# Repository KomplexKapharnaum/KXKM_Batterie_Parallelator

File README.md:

<h1 align="center">KXKM Batterie Parallelator</h1>

<p align="center">
  <strong>Battery Management Unit for parallel 24-30V packs</strong><br>
  Up to 32 batteries &middot; ESP32-S3 &middot; BLE + MQTT + InfluxDB &middot; iOS companion app
</p>

<p align="center">

</p>

---

## Overview

The **KXKM Batterie Parallelator** is an embedded Battery Management Unit (BMU) that safely parallels multiple battery packs (24-30V) for off-grid stage installations. Each battery is individually monitored (voltage, current, temperature) and can be disconnected in microseconds via MOSFET switches.

Built by [L'Electron Rare](https://lelectronrare.fr) for [KompleX KapharnaüM](https://komplex-kapharnaum.net) (Villeurbanne, France) — a live arts company deploying digital scenography in public spaces without grid power.

### Key Features

| Feature | Description |
|---------|-------------|
| Per-battery protection | Under/over-voltage, over-current, imbalance detection |
| Auto-reconnection | Exponential backoff with permanent lock after 5 faults |
| Soft-balancing | Duty-cycling with opportunistic R_int measurement |
| Victron integration | BLE Instant Readout + GATT SmartShunt emulation + device scanner |
| Touchscreen UI | 320x240 LVGL display with battery grid, SOH, charts |
| iOS companion app | BLE real-time monitoring, offline cache, role-based access |
| Cloud telemetry | MQTT + InfluxDB + Grafana with offline persistence |
| OTA updates | Dual-partition with automatic rollback |

---

## Quick Start

```bash
# ESP-IDF firmware (production)
cd firmware-idf
source ~/esp/esp-idf/export.sh
idf.py build
idf.py -p /dev/cu.usbmodem* flash monitor

# PlatformIO (legacy Arduino)
pio run -e kxkm-s3-16MB --target upload

# Run all tests (no hardware needed)
pio test -e sim-host          # 13 PlatformIO tests
cd firmware-idf && idf.py build  # 13 ESP-IDF host tests

# Cloud stack (kxkm-ai server)
cd kxkm-api && cp .env.example .env && docker compose up -d
```

---

## Architecture

```
                          ┌──────────────────────────┐
                          │    ESP32-S3-BOX-3         │
                          │    320x240 LVGL display   │
                          │    NimBLE + WiFi          │
                          └─────────┬────────────────┘
                                    │ I2C 50kHz
                    ┌───────────────┼───────────────┐
                    │               │               │
              ┌─────▼─────┐  ┌─────▼─────┐  ┌─────▼─────┐
              │ TCA9535    │  │ TCA9535   │  │  ...×8    │
              │ 4× MOSFET  │  │ 4× LED   │  │           │
              └─────┬─────┘  └───────────┘  └───────────┘
                    │
              ┌─────▼─────┐
              │ INA237 ×4  │  ← per TCA (voltage + current)
              └───────────┘

    ┌──────────────────────────────────────────────────────┐
    │                    Cloud Stack                        │
    │  BMU ──MQTT──► Mosquitto ──► Telegraf ──► InfluxDB   │
    │                                              │       │
    │  iPhone ◄──BLE──► BMU    Grafana ◄───────────┘       │
    │  iPhone ◄──REST──► FastAPI ◄─────────────────┘       │
    └──────────────────────────────────────────────────────┘
```

### Firmware Components (ESP-IDF, 25 modules)

| Component | Role |
|-----------|------|
| `bmu_protection` | State machine: 5 states, 5 criteria, permanent lock |
| `bmu_balancer` | Soft-balancing duty-cycling + R_int measurement |
| `bmu_ina237` | 16× INA237 power monitors (2mΩ shunt) |
| `bmu_tca9535` | 8× GPIO expanders (switches + LEDs) |
| `bmu_ble` | NimBLE 4 GATT services + Victron SmartShunt |
| `bmu_ble_victron` | Victron Instant Readout (AES-CTR encrypted ads) |
| `bmu_ble_victron_scan` | BLE central scanner for Victron devices |
| `bmu_display` | LVGL: battery grid, pack info, SOH, charts, swipe |
| `bmu_influx` + `_store` | InfluxDB client + offline FAT/SD persistence |
| `bmu_mqtt` | ESP-MQTT with auth credentials |
| `bmu_vedirect` | Victron VE.Direct UART parser (solar charger) |
| `bmu_rint` | Internal resistance pulse measurement |
| `bmu_web` | HTTP + WebSocket with token auth + rate limiting |
| `bmu_config` | NVS runtime config + Victron device keys |
| `bmu_storage` | NVS, FAT, SPIFFS, SD card, USB MSC |
| `bmu_ota` | OTA firmware update with rollback |

### Protection Logic

```
Nb_switch < 5   →  Reconnect immediately when condition clears
Nb_switch == 5  →  10-second delay before reconnection
Nb_switch > 5   →  Permanent lock (blinking red LED) until reboot
```

| Threshold | Default | Configurable |
|-----------|---------|:------------:|
| Min voltage | 24,000 mV | via Kconfig + NVS |
| Max voltage | 30,000 mV | via Kconfig + NVS |
| Max current | 10,000 mA | via Kconfig + NVS |
| Imbalance | 1,000 mV | via Kconfig + NVS |
| Reconnect delay | 10,000 ms | via Kconfig |
| Switch limit | 5 | via Kconfig |

### LED Behavior

| State | LED |
|-------|-----|
| Connected | Solid green |
| Disconnected | Solid red |
| Error | **Blinking red** (~1 Hz) |
| Locked | Solid red |

---

## iOS Companion App

<p align="center">
  <strong>KXKM BMU</strong> &mdash; SwiftUI + CoreBluetooth
</p>

| Feature | Transport |
|---------|-----------|
| Real-time battery dashboard | BLE (2s poll) |
| Battery detail + voltage chart | BLE |
| Switch ON/OFF + reset | BLE (role-gated) |
| Protection config (0.025V/A step) | BLE |
| WiFi config for BMU | BLE |
| Audit trail + filtering | Local SQLDelight |
| Offline mode with cache indicator | Auto-fallback |
| SOH dashboard + R_int | BLE + REST |
| Victron device scanning | BLE passive |

**3 roles**: Admin (full), Technician (control), Viewer (read-only) — PIN + Face ID.

**Code**: `iosApp/` (Xcode, CoreBluetooth) + `kxkm-bmu-app/` (KMP Shared Kotlin)

---

## Victron BLE Integration

The BMU interacts with the Victron ecosystem via three mechanisms:

| Mechanism | Direction | Protocol |
|-----------|-----------|----------|
| Instant Readout | BMU → VictronConnect | AES-CTR encrypted advertising (PID 0xA389) |
| GATT SmartShunt | BMU → any BLE client | 9 read-only characteristics (V, I, SOC, Ah, TTG, T, alarm) |
| Device Scanner | Victron devices → BMU | Passive BLE scan, AES decrypt, 8 device cache |

Supported Victron record types: Solar (0x01), Battery (0x02), Inverter (0x03), DC-DC (0x04).

---

## Cloud Infrastructure

Docker stack on `kxkm-ai` server:

| Service | Port | Role |
|---------|------|------|
| Mosquitto | 1883, 9001 | MQTT broker (authenticated) |
| InfluxDB 2.7 | 8086 | Time-series storage (org=kxkm, bucket=bmu) |
| Telegraf | - | MQTT → InfluxDB bridge |
| FastAPI | 8400 | REST API (sync, history, audit) |
| Grafana 11 | 3001 | 3 dashboards (live, fleet, solar) |

**Setup**: `cp .env.example .env` — fill all secrets (API key, InfluxDB token, MQTT credentials, Grafana password, CORS origins). All secrets via `${...}` env vars, `chmod 600 .env`.

**Offline resilience**: when WiFi/InfluxDB is unreachable, telemetry is persisted to internal FAT flash (`/fatfs/influx/`) with 2-file rotation (512KB each). Automatic replay on reconnection.

---

## Testing

**26 tests total** — no hardware required.

### PlatformIO sim-host (13 tests)

```bash
pio test -e sim-host
```

| Suite | Tests | Covers |
|-------|:-----:|--------|
| `test_protection` | 10 | V/I/imbalance/lock state machine |
| `test_battery_route_validation` | - | Index bounds + state checks |
| `test_influx_buffer_codec` | - | InfluxDB line-protocol encoding |
| `test_web_mutation_rate_limit` | 3 | Sliding window + multi-IP |
| `test_web_route_security` | 9 | Constant-time token + Bearer |
| `test_ws_auth_flow` | 7 | Combined auth + rate limit |
| `test_mqtt_influx_codec` | 3 | JSON MQTT + topic parsing |
| `test_emulation_bench` | - | Emulation benchmark |

### ESP-IDF Host Tests (13 tests)

```bash
cd firmware-idf && idf.py build
```

| Suite | Tests | Covers |
|-------|:-----:|--------|
| `test_protection` | 13 | Full state machine (ESP-IDF) |
| `test_victron_gatt` | 8 | GATT encoding (V, SOC, alarm, TTG, T) |
| `test_victron_scan` | 5 | Payload parsing, expiry, MAC, CID |
| `test_ble_victron` | - | Battery/solar payload encoding |
| `test_vedirect_parser` | - | VE.Direct frame parsing |
| `test_rint` | - | R_int calculation |
| `test_config_labels` | - | Battery label management |
| `test_vrm_topics` | - | VRM topic generation |

### CI/CD Pipelines

| Pipeline | Trigger | Gate |
|----------|---------|------|
| `ci.yml` | push/PR | sim-host 13 tests pass |
| `sim-host-tests.yml` | push/PR | + S3 build + RAM ≤75% + Flash ≤85% |
| `esp-idf-ci.yml` | push/PR | + ESP-IDF host tests + flash ≤85% of 2MB OTA |

**Current flash usage**: 81% (1.69 MB / 2 MB OTA partition) — 19% headroom.

---

## Security Audit

**All findings resolved** as of 2026-04-07.

<details>
<summary><strong>Phase 1 — Migration (March 2026): 7/7 resolved</strong></summary>

| ID | Finding | Status |
|----|---------|--------|
| CRIT-001 | Obsolete function calls | ✅ |
| CRIT-002 | Unreliable global Nb_INA | ✅ |
| CRIT-003 | I2C access without mutex | ✅ |
| CRIT-004 | Missing mutex init | ✅ |
| HIGH-005 | WebSocket V/I race | ✅ |
| HIGH-006 | reconnect_time race | ✅ |
| HIGH-007 | Uninitialized globals | ✅ |

</details>

<details>
<summary><strong>Phase 2 — Deep audit (March-April 2026): 13/13 resolved</strong></summary>

| ID | Severity | Finding | Fix |
|----|----------|---------|-----|
| CRIT-A | Critical | mV/V unit mismatch | ESP-IDF: mV everywhere |
| CRIT-B | Critical | Imbalance vs config instead of fleet max | bmu_protection |
| CRIT-C | Critical | Deadlock in web switch | bmu_web |
| CRIT-D | Critical | Unauthenticated routes | bmu_web_security |
| HIGH-1 | High | Negative overcurrent ignored | Bidirectional factor |
| HIGH-2 | High | Unauthenticated WebSocket | Token on first frame |
| HIGH-3 | High | XSS in /log | cJSON null check |
| HIGH-4 | High | MQTT plaintext | Mosquitto auth + .env |
| HIGH-5 | High | I2C speed change unguarded | I2CLockGuard |
| HIGH-7 | High | Public battery_voltages[] | state_mutex |
| HIGH-8 | High | Influx task crash on SD fail | influx_store fallback |
| MED-1 | Medium | No permanent lock (F08) | BMU_STATE_LOCKED |
| MED-010 | Medium | mV/V harmonization | mV throughout |

</details>

<details>
<summary><strong>Infrastructure audit (April 2026): 5/5 resolved</strong></summary>

| Finding | Fix |
|---------|-----|
| Mosquitto anonymous access | Auth + password file |
| Hardcoded secrets in docker-compose | All via .env (chmod 600) |
| Default InfluxDB token | Rotated (44-char random) |
| CORS allow_origins=["*"] | Restricted via env var |
| Offline data loss | FAT/SD persistence + replay |

</details>

---

## Hardware

### PCB Revisions

| Version | Status | Files |
|---------|--------|-------|
| BMU v1 | Manufactured | `hardware/PCB/` |
| BMU v2 | Production-ready (ERC 0, BOM 107) | `hardware/pcb-bmu-v2/` |

### Key ICs

| IC | Package | Role | I2C Address |
|----|---------|------|-------------|
| INA237 | VSSOP-10 | Power monitor (V/I/P) | 0x40-0x4F (16 max) |
| TCA9535 | TSSOP-24 | GPIO expander (switches + LEDs) | 0x20-0x27 (8 max) |
| ISO1540 | SOIC-8 | Galvanic I2C isolator | - |
| IRF4905 | D2PAK | P-channel MOSFET (55V, 74A) | - |

### I2C Mapping

```
TCA_0 (0x20) → INA 0x40-0x43 → Batteries 1-4
TCA_1 (0x21) → INA 0x44-0x47 → Batteries 5-8
TCA_2 (0x22) → INA 0x48-0x4B → Batteries 9-12
TCA_3 (0x23) → INA 0x4C-0x4F → Batteries 13-16
```

Topology constraint: `Nb_TCA × 4 == Nb_INA` — mismatch triggers fail-safe (all OFF).

---

## Project Structure

```
KXKM_Batterie_Parallelator/
├── firmware-idf/          # ESP-IDF 5.4 firmware (25 components)
│   ├── components/        # Modular ESP-IDF components
│   ├── main/              # app_main entry point
│   └── test/              # Unity host tests (13 suites)
├── firmware/              # Legacy PlatformIO/Arduino firmware
│   ├── src/               # Source modules
│   ├── test/              # sim-host tests (8 suites, 13 tests)
│   └── lib/INA237/        # Local INA237 driver fork
├── iosApp/                # iOS SwiftUI app (CoreBluetooth)
├── kxkm-bmu-app/          # KMP shared Kotlin module
│   └── shared/            # Cross-platform domain logic
├── kxkm-api/              # Docker stack (Mosquitto, InfluxDB, FastAPI, Grafana)
├── hardware/              # KiCad schematics + Gerbers (v1 + v2)
├── specs/                 # Kill_LIFE gates (S0-S3)
├── docs/                  # Specs, plans, governance, research
├── grafana/dashboards/    # 3 Grafana dashboard JSONs
└── scripts/               # CI, QA, ML pipeline
```

---

## About KompleX KapharnaüM

[KompleX KapharnaüM](https://komplex-kapharnaum.net) is a live arts company based in Villeurbanne (Lyon, France), active for 20+ years in street arts, live performance, and digital creation. The company develops its own embedded hardware platform (K32, ESP32-based) and maintains open-source tools on [GitHub](https://github.com/KomplexKapharnaum).

---

## License

[GNU General Public License v3.0](LICENSE)

---

<p align="center">
  <sub>Built with ESP-IDF, LVGL, NimBLE, SwiftUI, FastAPI, InfluxDB, and Grafana.</sub><br>
  <sub>Developed by <a href="https://lelectronrare.fr">L'Electron Rare</a> for <a href="https://komplex-kapharnaum.net">KompleX KapharnaüM</a></sub>
</p>

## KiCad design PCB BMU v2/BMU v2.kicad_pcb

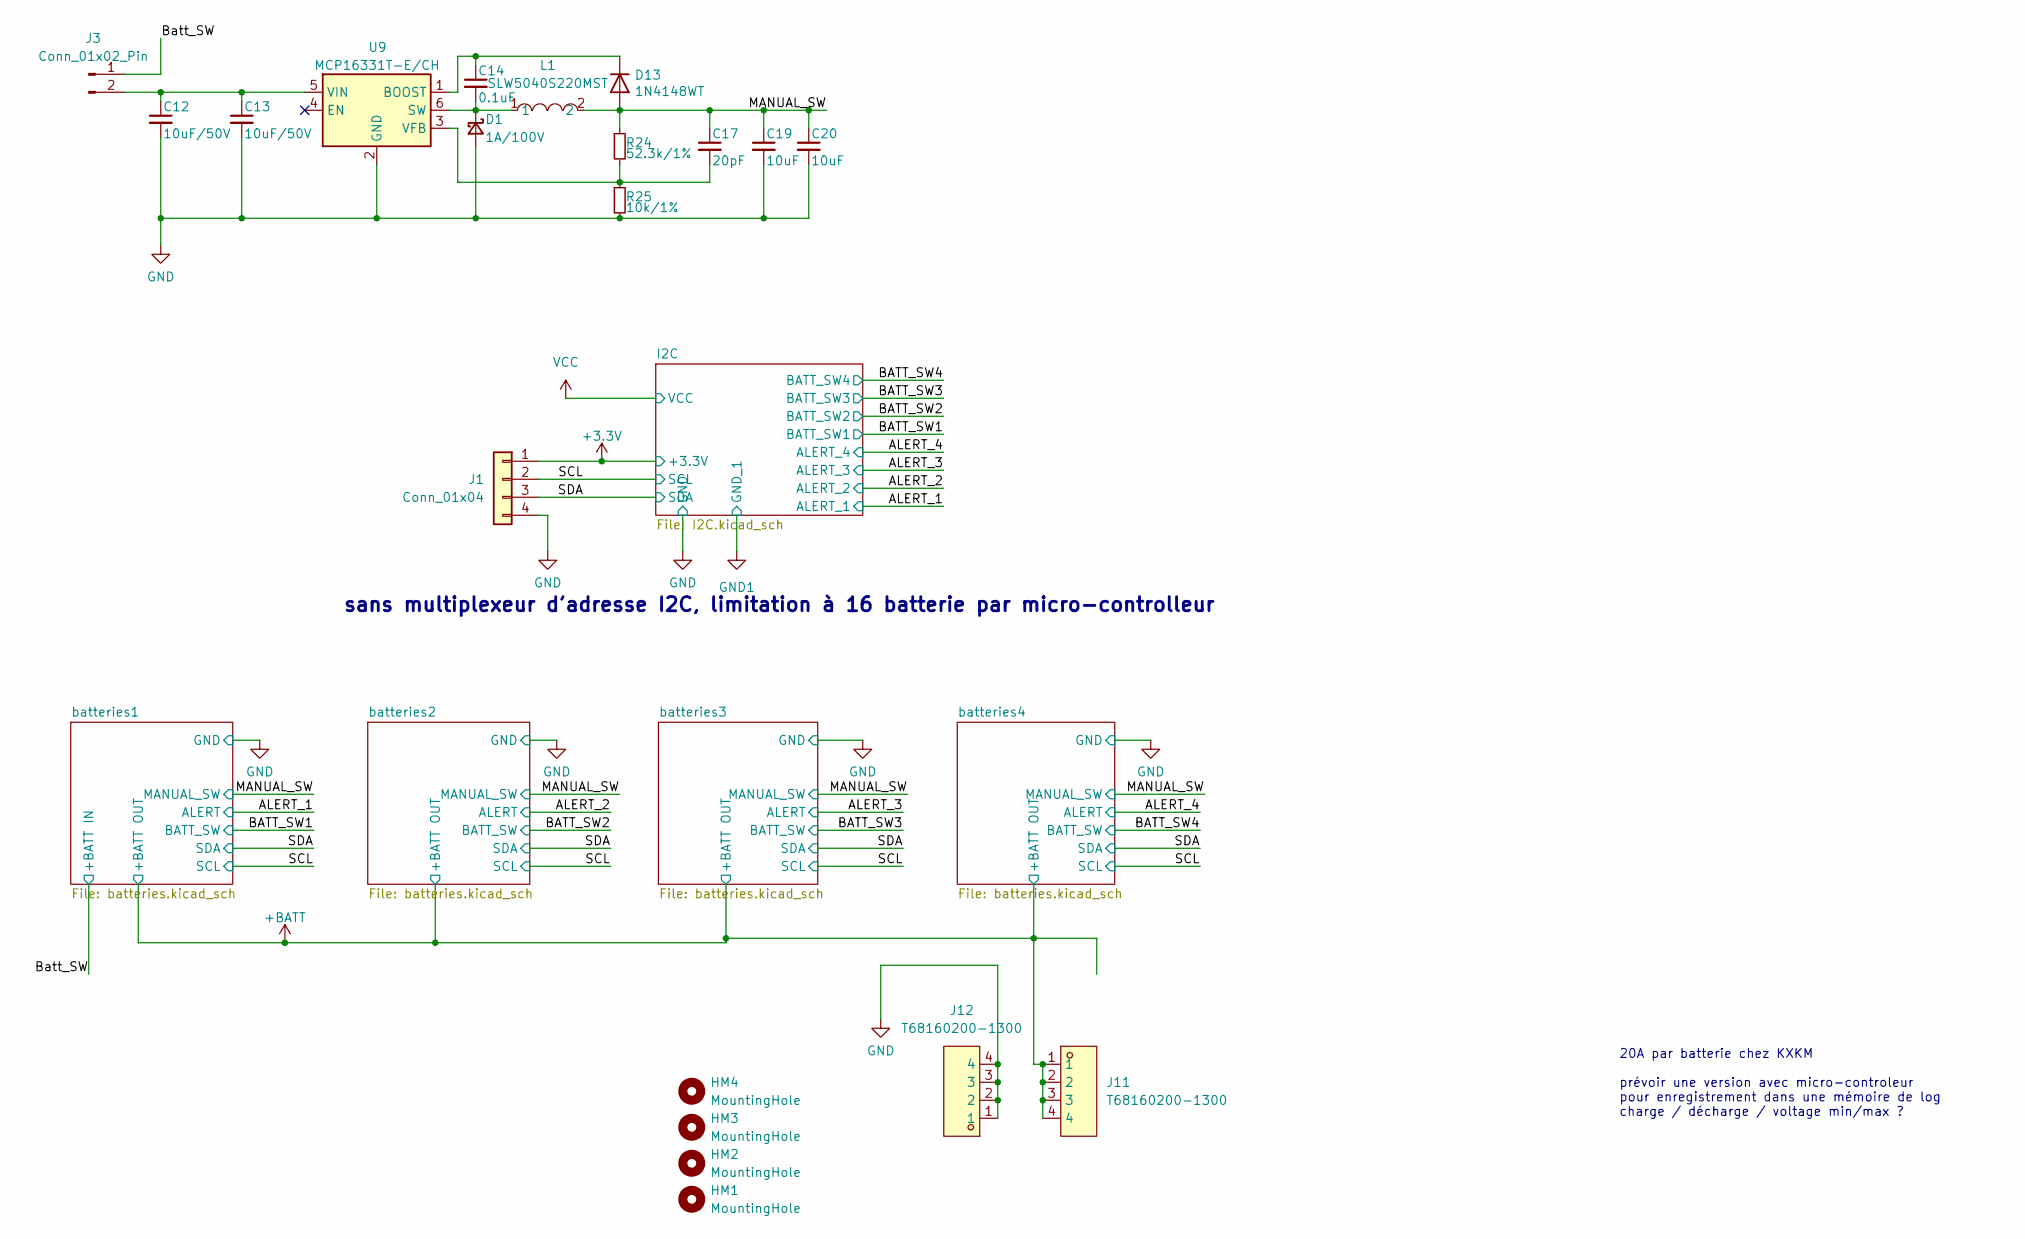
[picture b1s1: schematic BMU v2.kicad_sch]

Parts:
C12, C13: 10uF/50V; C_1206_3216Metric; LCSC C13585
C14: 0.1uF; C_0603_1608Metric; LCSC C14663
C17: 20pF; C_0603_1608Metric; LCSC C1648
C19, C20: 10uF; C_0805_2012Metric
D1: 1A/100V; D_SMA; LCSC C14996
D13: 1N4148WT; D_SOD-523; LCSC C68948
HM1, HM2, HM3, HM4: MountingHole; MountingHole_2.7mm_M2.5
J1: Conn_01x04; PinSocket_1x04_P2.54mm_Vertical
J3: Conn_01x02_Pin; PinHeader_1x02_P2.54mm_Vertical
J11, J12: T68160200-1300; TH-8_L20.0-W16.0-P5.60_AMT0860001TA0000G; LCSC Part C19724545
L1: SLW5040S220MST; IND-SMD_L5.0-W5.0; LCSC Part C182167
R24: 52.3k/1%; R_0603_1608Metric
R25: 10k/1%; R_0603_1608Metric; LCSC C25804
U9: MCP16331T-E/CH; SOT-23-6; LCSC C105695

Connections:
+3.3V: J1.1; also elsewhere on the board
+BATT: J11.1, J11.2, J11.3, J11.4; also elsewhere on the board
/Batt_SW: J3.1; also elsewhere on the board
/MANUAL_SW: C17.1, C19.1, C20.1, D13.2 (A), L1.2, R24.1; also elsewhere on the board
/SCL: J1.2; also elsewhere on the board
/SDA: J1.3; also elsewhere on the board
GND: C12.2, C13.2, C19.2, C20.2, D1.2 (A), J1.4, J12.1, J12.2, J12.3, J12.4, R25.2, U9.2 (GND); also elsewhere on the board
unnamed: C14.2, D1.1 (K), L1.1, U9.6 (SW)
unnamed: C14.1, D13.1 (K), U9.1 (BOOST)
unnamed: C12.1, C13.1, J3.2, U9.5 (VIN)
unnamed: C17.2, R24.2, R25.1, U9.3 (VFB)

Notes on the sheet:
20A par batterie chez KXKM prévoir une version avec micro-controleur pour enregistrement dans une mémoire de log charge / décharge / voltage min/max ?
sans multiplexeur d'adresse I2C, limitation à 16 batterie par micro-controlleur

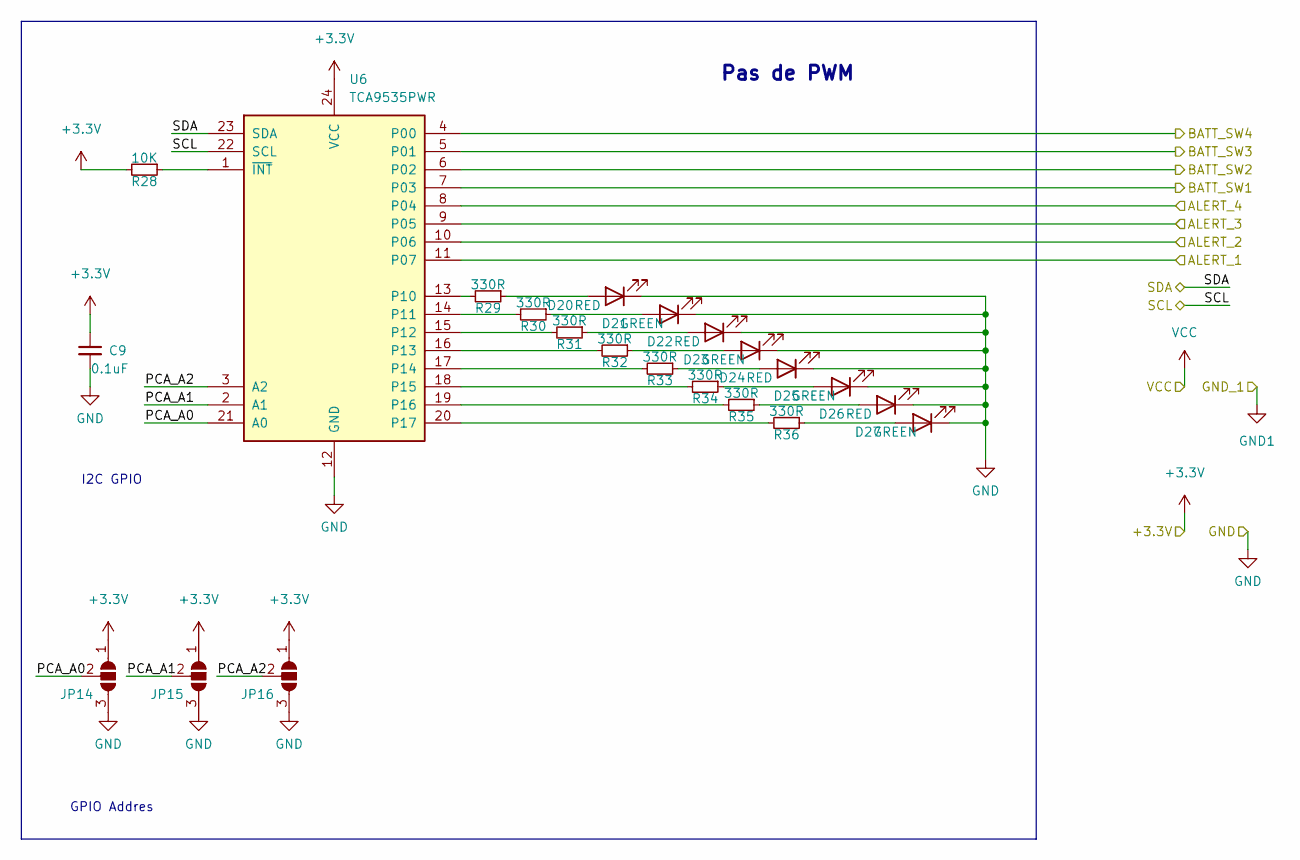
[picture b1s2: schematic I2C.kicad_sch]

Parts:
C9: 0.1uF; C_0402_1005Metric; LCSC C307331
D20, D22, D24, D26: RED; LED_0603_1608Metric
D21, D23, D25, D27: GREEN; LED_0603_1608Metric
JP14, JP15, JP16: SolderJumper_3_Open; SolderJumper-3_P1.3mm_Open_RoundedPad1.0x1.5mm_NumberLabels
R28: 10K; R_0603_1608Metric
R29, R30, R31, R32, R33, R34, R35, R36: 330R; R_0603_1608Metric
U6: TCA9535PWR; TSSOP-24_4.4x7.8mm_P0.65mm

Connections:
+3.3V: C9.1, JP14.1 (A), JP15.1 (A), JP16.1 (A), R28.2, U6.24 (VCC); also elsewhere on the board
/ALERT_1: U6.11 (P07); also elsewhere on the board
/ALERT_2: U6.10 (P06); also elsewhere on the board
/ALERT_3: U6.9 (P05); also elsewhere on the board
/ALERT_4: U6.8 (P04); also elsewhere on the board
/BATT_SW1: U6.7 (P03); also elsewhere on the board
/BATT_SW2: U6.6 (P02); also elsewhere on the board
/BATT_SW3: U6.5 (P01); also elsewhere on the board
/BATT_SW4: U6.4 (P00); also elsewhere on the board
/I2C/PCA_A0: JP14.2 (C), U6.21 (A0)
/I2C/PCA_A1: JP15.2 (C), U6.2 (A1)
/I2C/PCA_A2: JP16.2 (C), U6.3 (A2)
/SCL: U6.22 (SCL); also elsewhere on the board
/SDA: U6.23 (SDA); also elsewhere on the board
GND: C9.2, D20.1 (K), D21.1 (K), D22.1 (K), D23.1 (K), D24.1 (K), D25.1 (K), D26.1 (K), D27.1 (K), JP14.3 (B), JP15.3 (B), JP16.3 (B), U6.12 (GND); also elsewhere on the board
unnamed: D20.2 (A), R29.1
unnamed: D21.2 (A), R30.1
unnamed: D22.2 (A), R31.1
unnamed: D23.2 (A), R32.1
unnamed: D24.2 (A), R33.1
unnamed: D25.2 (A), R34.1
unnamed: D26.2 (A), R35.1
unnamed: D27.2 (A), R36.1
unnamed: R29.2, U6.13 (P10)
unnamed: R30.2, U6.14 (P11)
unnamed: R31.2, U6.15 (P12)
unnamed: R32.2, U6.16 (P13)
unnamed: R33.2, U6.17 (P14)
unnamed: R34.2, U6.18 (P15)
unnamed: R35.2, U6.19 (P16)
unnamed: R36.2, U6.20 (P17)
unnamed: R28.1, U6.1 (~INT)

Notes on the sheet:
I2C GPIO
Pas de PWM
GPIO Addres

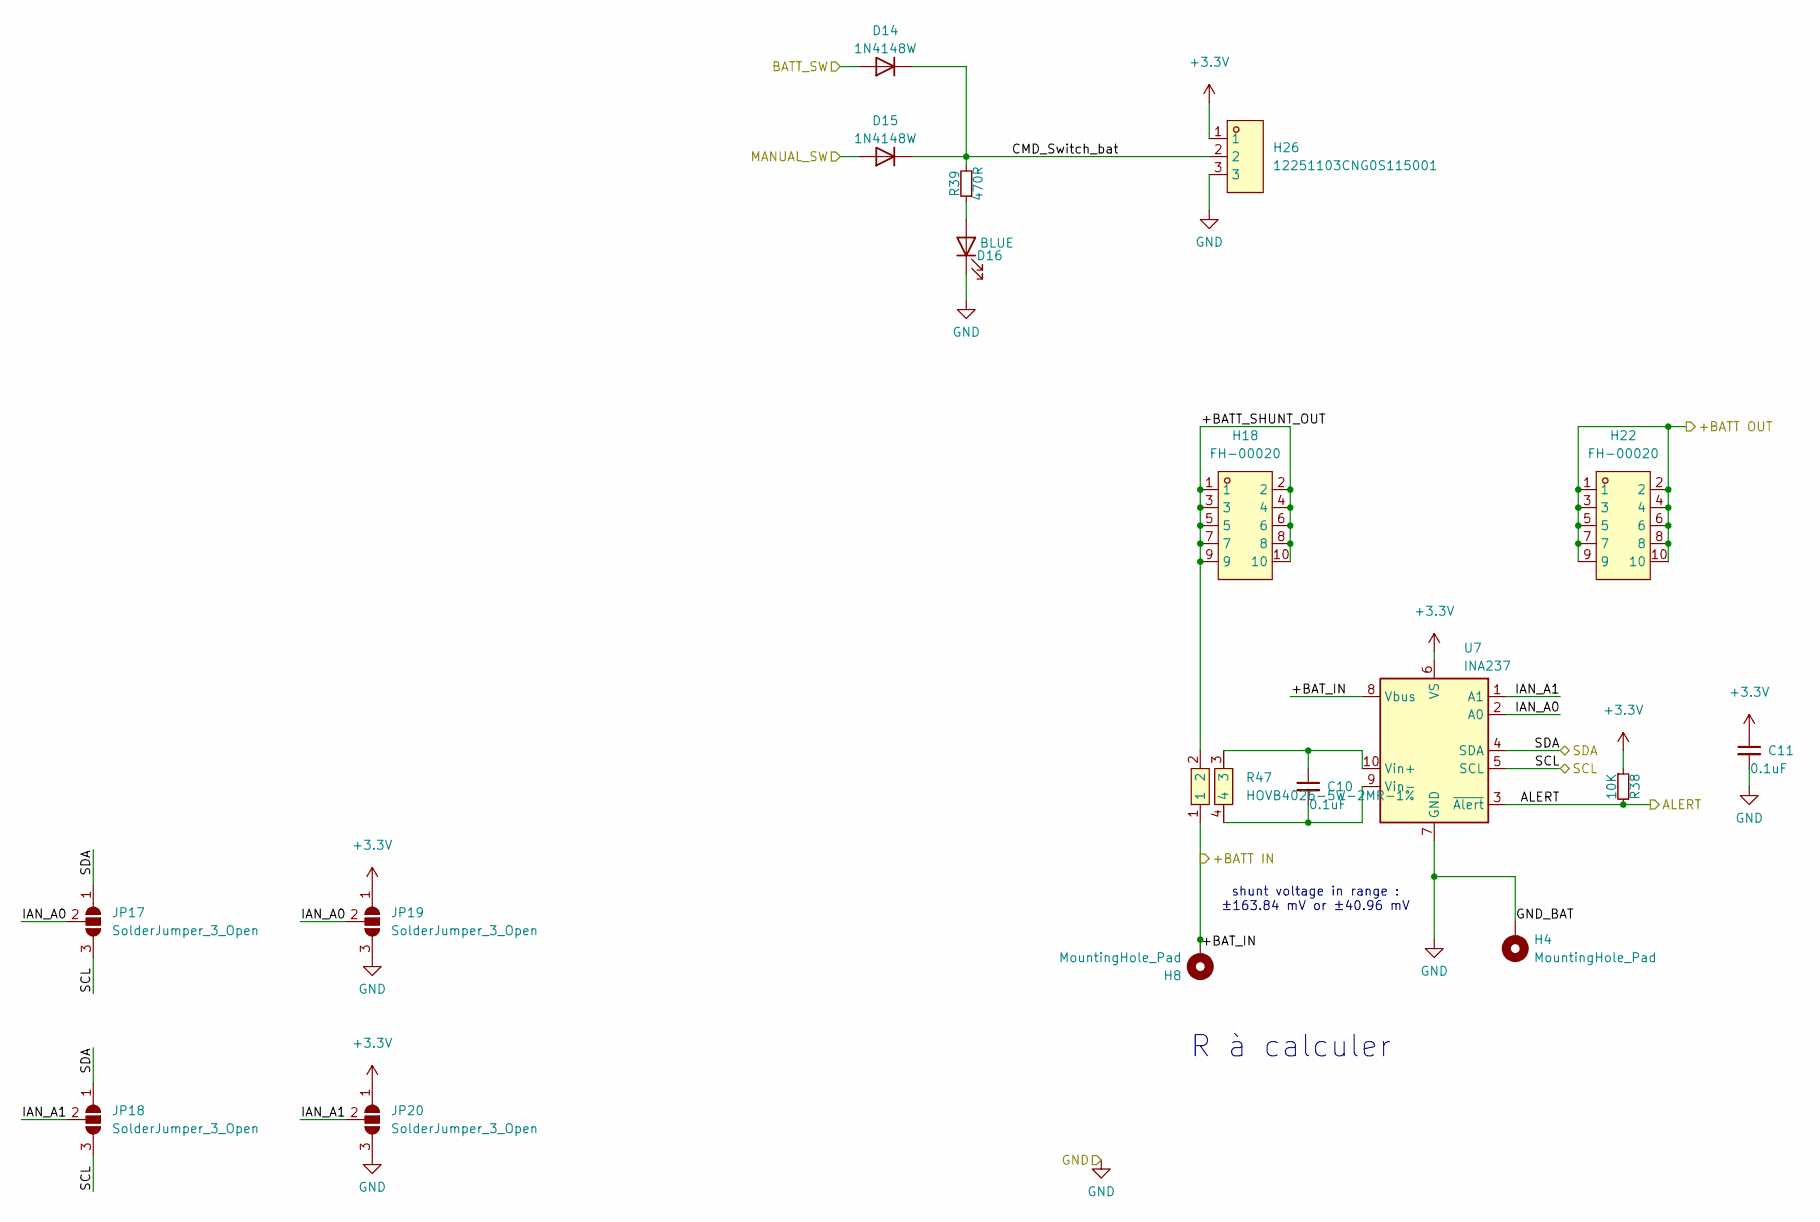
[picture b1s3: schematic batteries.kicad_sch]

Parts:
C10: 0.1uF; C_0805_2012Metric
C11: 0.1uF; C_0402_1005Metric; LCSC C1525
D14, D15: 1N4148W; D_SOD-523
D16: BLUE; LED_0603_1608Metric
H4, H8: MountingHole_Pad; MountingHole_5mm_Pad
H18, H22: FH-00020; HDR-TH_10P-P2.54-V-F-R2-C5-S2.54; LCSC Part C2685204
H26: 12251103CNG0S115001; HDR-TH_3P-P2.54-V-M-1; LCSC Part C429954
JP17, JP18, JP19, JP20: SolderJumper_3_Open; SolderJumper-3_P1.3mm_Open_RoundedPad1.0x1.5mm_NumberLabels
R38: 10K; R_0603_1608Metric
R39: 470R; R_0603_1608Metric
R47: HOVB4026-5W-2MR-1%; RES-SMD_4P-L10.8-W6.7; LCSC Part C481536
U7: INA237; VSSOP-10_3x3mm_P0.5mm

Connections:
+3.3V: C11.1, H26.1, JP19.1 (A), JP20.1 (A), R38.1, U7.6 (VS); also elsewhere on the board
+BATT: H22.1, H22.2, H22.3, H22.4, H22.5, H22.6, H22.7, H22.8, H22.9, H22.10; also elsewhere on the board
/ALERT_4: R38.2, U7.3 (~Alert); also elsewhere on the board
/BATT_SW4: D14.2 (A); also elsewhere on the board
/MANUAL_SW: D15.2 (A); also elsewhere on the board
/SCL: JP17.3 (B), JP18.3 (B), U7.5 (SCL); also elsewhere on the board
/SDA: JP17.1 (A), JP18.1 (A), U7.4 (SDA); also elsewhere on the board
/batteries4/+BATT_SHUNT_OUT: H18.1, H18.2, H18.3, H18.4, H18.5, H18.6, H18.7, H18.8, H18.9, H18.10, R47.2
/batteries4/+BAT_IN: H8.1, R47.1, U7.8 (Vbus)
/batteries4/CMD_Switch_bat: D14.1 (K), D15.1 (K), H26.2, R39.2
/batteries4/IAN_A0: JP17.2 (C), JP19.2 (C), U7.2 (A0)
/batteries4/IAN_A1: JP18.2 (C), JP20.2 (C), U7.1 (A1)
GND: C11.2, D16.1 (K), H4.1, H26.3, JP19.3 (B), JP20.3 (B), U7.7 (GND); also elsewhere on the board
unnamed: D16.2 (A), R39.1
unnamed: C10.1, R47.3, U7.10 (Vin+)
unnamed: C10.2, R47.4, U7.9 (Vin-)

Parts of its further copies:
C2, C4, C6: 0.1uF; C_0805_2012Metric
C3, C5, C7: 0.1uF; C_0402_1005Metric; LCSC C1525
D2, D3, D6, D7, D10, D11: 1N4148W; D_SOD-523
D4, D8, D12: BLUE; LED_0603_1608Metric
H1, H2, H3, H5, H6, H7: MountingHole_Pad; MountingHole_5mm_Pad
H15, H16, H17, H19, H20, H21: FH-00020; HDR-TH_10P-P2.54-V-F-R2-C5-S2.54; LCSC Part C2685204
H23, H24, H25: 12251103CNG0S115001; HDR-TH_3P-P2.54-V-M-1; LCSC Part C429954
JP2, JP3, JP4, JP5, JP6, JP7, JP8, JP9, JP10, JP11, JP12, JP13: SolderJumper_3_Open; SolderJumper-3_P1.3mm_Open_RoundedPad1.0x1.5mm_NumberLabels
R1, R8, R46: HOVB4026-5W-2MR-1%; RES-SMD_4P-L10.8-W6.7; LCSC Part C481536
R5, R12, R19: 470R; R_0603_1608Metric
R17, R18, R37: 10K; R_0603_1608Metric
U1, U2, U3: INA237; VSSOP-10_3x3mm_P0.5mm

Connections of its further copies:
+3.3V: C3.1, C5.1, C7.1, H23.1, H24.1, H25.1, JP4.1 (A), JP5.1 (A), JP8.1 (A), JP9.1 (A), JP12.1 (A), JP13.1 (A), R17.1, R18.1, R37.1, U1.6 (VS), U2.6 (VS), U3.6 (VS); also elsewhere on the board
+BATT: H19.1, H19.2, H19.3, H19.4, H19.5, H19.6, H19.7, H19.8, H19.9, H19.10, H20.1, H20.2, H20.3, H20.4, H20.5, H20.6, H20.7, H20.8, H20.9, H20.10, H21.1, H21.2, H21.3, H21.4, H21.5, H21.6, H21.7, H21.8, H21.9, H21.10; also elsewhere on the board
/ALERT_1: R17.2, U1.3 (~Alert); also elsewhere on the board
/ALERT_2: R18.2, U2.3 (~Alert); also elsewhere on the board
/ALERT_3: R37.2, U3.3 (~Alert); also elsewhere on the board
/BATT_SW1: D2.2 (A); also elsewhere on the board
/BATT_SW2: D6.2 (A); also elsewhere on the board
/BATT_SW3: D10.2 (A); also elsewhere on the board
/Batt_SW: H5.1, R1.1, U1.8 (Vbus); also elsewhere on the board
/MANUAL_SW: D3.2 (A), D7.2 (A), D11.2 (A); also elsewhere on the board
/SCL: JP2.3 (B), JP3.3 (B), JP6.3 (B), JP7.3 (B), JP10.3 (B), JP11.3 (B), U1.5 (SCL), U2.5 (SCL), U3.5 (SCL); also elsewhere on the board
/SDA: JP2.1 (A), JP3.1 (A), JP6.1 (A), JP7.1 (A), JP10.1 (A), JP11.1 (A), U1.4 (SDA), U2.4 (SDA), U3.4 (SDA); also elsewhere on the board
/batteries1/+BATT_SHUNT_OUT: H15.1, H15.2, H15.3, H15.4, H15.5, H15.6, H15.7, H15.8, H15.9, H15.10, R1.2
/batteries1/CMD_Switch_bat: D2.1 (K), D3.1 (K), H23.2, R5.2
/batteries1/IAN_A0: JP2.2 (C), JP4.2 (C), U1.2 (A0)
/batteries1/IAN_A1: JP3.2 (C), JP5.2 (C), U1.1 (A1)
/batteries2/+BATT_SHUNT_OUT: H16.1, H16.2, H16.3, H16.4, H16.5, H16.6, H16.7, H16.8, H16.9, H16.10, R8.2
/batteries2/+BAT_IN: H6.1, R8.1, U2.8 (Vbus)
/batteries2/CMD_Switch_bat: D6.1 (K), D7.1 (K), H24.2, R12.2
/batteries2/IAN_A0: JP6.2 (C), JP8.2 (C), U2.2 (A0)
/batteries2/IAN_A1: JP7.2 (C), JP9.2 (C), U2.1 (A1)
/batteries3/+BATT_SHUNT_OUT: H17.1, H17.2, H17.3, H17.4, H17.5, H17.6, H17.7, H17.8, H17.9, H17.10, R46.2
/batteries3/+BAT_IN: H7.1, R46.1, U3.8 (Vbus)
/batteries3/CMD_Switch_bat: D10.1 (K), D11.1 (K), H25.2, R19.2
/batteries3/IAN_A0: JP10.2 (C), JP12.2 (C), U3.2 (A0)
/batteries3/IAN_A1: JP11.2 (C), JP13.2 (C), U3.1 (A1)
GND: C3.2, C5.2, C7.2, D4.1 (K), D8.1 (K), D12.1 (K), H1.1, H2.1, H3.1, H23.3, H24.3, H25.3, JP4.3 (B), JP5.3 (B), JP8.3 (B), JP9.3 (B), JP12.3 (B), JP13.3 (B), U1.7 (GND), U2.7 (GND), U3.7 (GND); also elsewhere on the board
unnamed: D4.2 (A), R5.1
unnamed: D8.2 (A), R12.1
unnamed: D12.2 (A), R19.1
unnamed: C2.1, R1.3, U1.10 (Vin+)
unnamed: C2.2, R1.4, U1.9 (Vin-)
unnamed: C4.1, R8.3, U2.10 (Vin+)
unnamed: C4.2, R8.4, U2.9 (Vin-)
unnamed: C6.1, R46.3, U3.10 (Vin+)
unnamed: C6.2, R46.4, U3.9 (Vin-)

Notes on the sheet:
R à calculer
shunt voltage in range : ±163.84 mV or ±40.96 mV

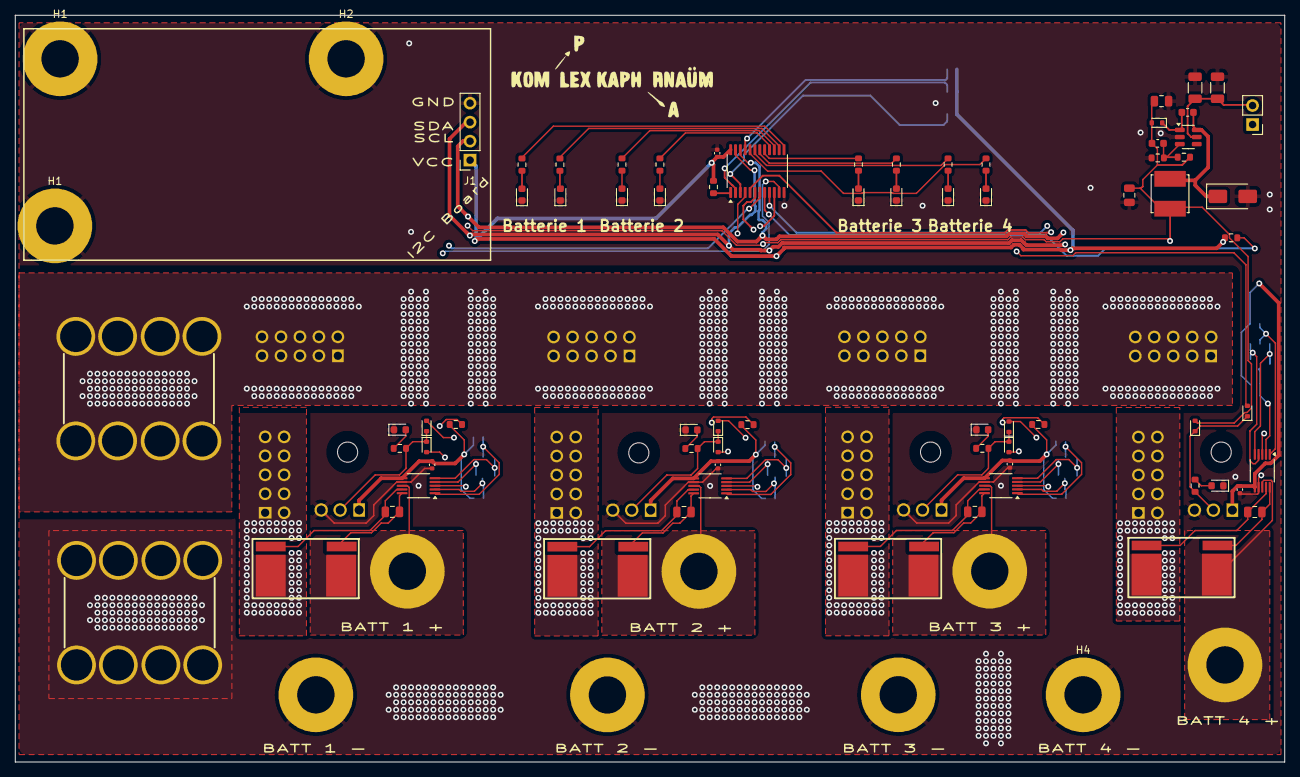
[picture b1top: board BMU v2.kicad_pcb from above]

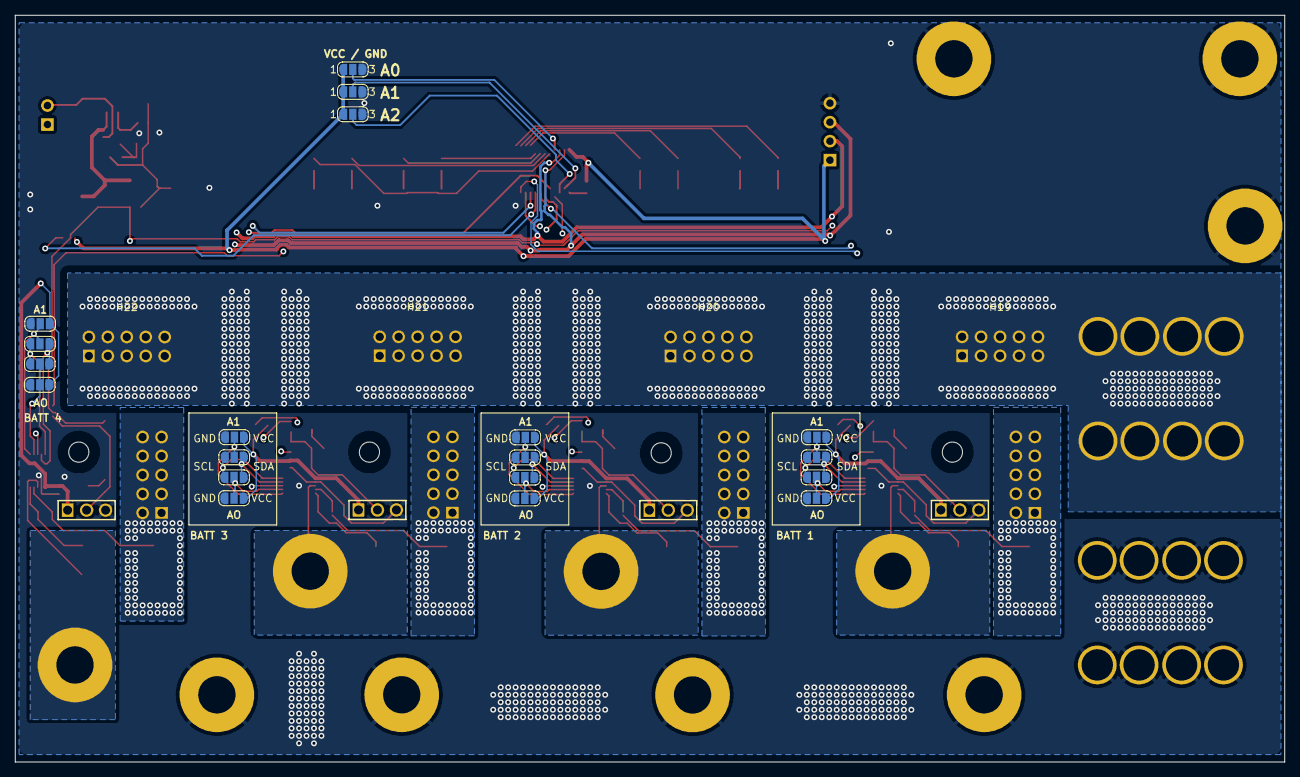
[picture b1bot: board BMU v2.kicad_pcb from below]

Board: 4 copper layers, 170.0 x 100.0 mm, 117 parts (35 on the bottom side), 70 nets.

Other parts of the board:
H1#2, H1#3, H2#2: MountingHole_Pad; MountingHole_5mm_Pad

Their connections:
GND: H1#2.1, H1#3.1, H2#2.1; also elsewhere on the board

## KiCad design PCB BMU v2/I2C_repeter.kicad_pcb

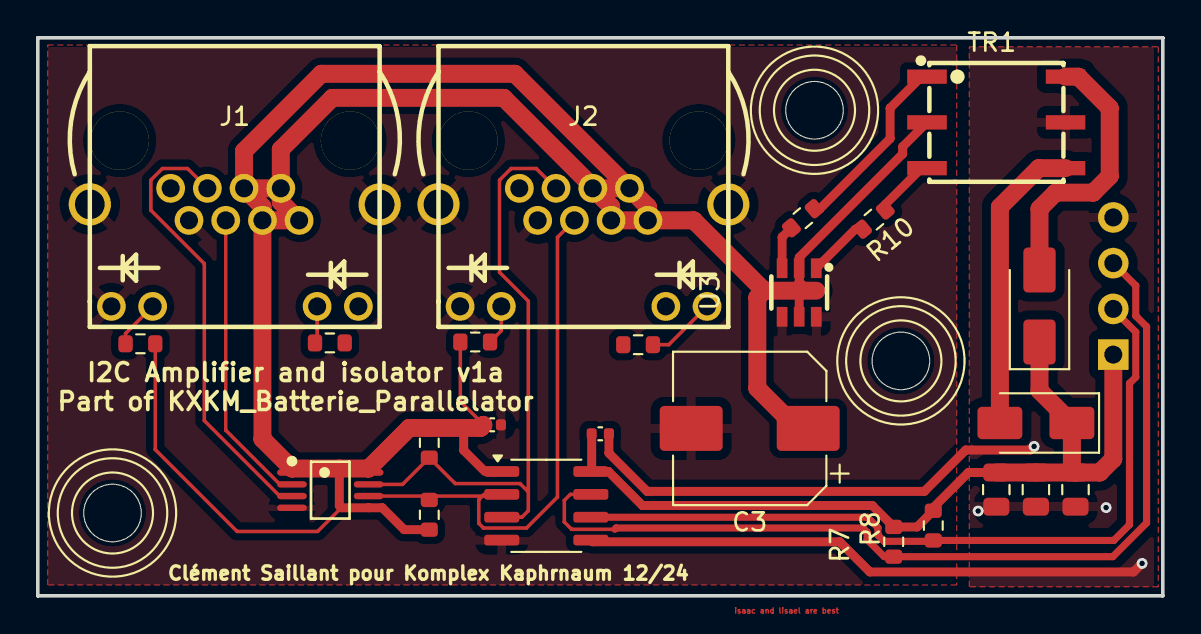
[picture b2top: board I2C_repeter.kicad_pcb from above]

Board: 2 copper layers, 62.5 x 31.0 mm, 28 parts (1 on the bottom side), 20 nets.

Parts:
C1, C2: 0.1uF; C_0402_1005Metric
C3: 10uF,16V; CP_Elec_8x10
C4: 0,1uF; C_0805_2012Metric
C5: 1uF; C_0805_2012Metric
C6: 10uF; C_0805_2012Metric
D1, D2: 1A/100V; D_SMA
H1, H2, H3: MountingHole; MountingHole_3.2mm_M3
J1, J2: RJ45_Shielded; RJ45-TH_RC01061
J3: Conn_01x04; PinHeader_1x04_P2.54mm_Vertical
R1, R2, R5, R6: 470R; R_0603_1608Metric
R3, R4: 10K; R_0603_1608Metric
R7, R8: 1K; R_0603_1608Metric
R9, R10: 50R; R_0603_1608Metric
TR1: VPT85BB-01A; XFMR-SMD_L7.5-W6.7-P2.54-LS7.7-BL
U1: TCA9517ADGK; VSSOP-8_L3.0-W3.0-P0.65-LS5.0-BL
U2: ISO1540DR; SOIC-8_3.9x4.9mm_P1.27mm
U3: VPS8505; SOT-23-6_L2.9-W1.6-P0.95-LS2.8-BR

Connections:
+3.3V: C2.1, C4.1, C5.1, C6.1, D1.1 (K), D2.1 (K), J3.1, R7.2, R8.2, U2.8 (VCC2)
/SCL: J3.2, R8.1, U2.6 (SCL2)
/SCL1: J2.3, R3.1, U1.7 (SCLB), U2.3 (SCL1)
/SDA: J3.3, R7.1, U2.7 (SDA2)
/SDA1: J2.4, R4.1, U1.6 (SDAB), U2.2 (SDA1)
GND: C2.2, C4.2, C5.2, C6.2, J3.4, TR1.5, U2.5 (GND2)
GND1: C1.2, C3.2, J1.1, J1.2, J1.9 (LEDG-), J1.13, J1.14, J2.1, J2.2, J2.9 (LEDG-), J2.13, J2.14, U1.4 (GND), U2.4 (GND1), U3.4 (GND), U3.6 (CLK)
unnamed: D1.2 (A), TR1.6
unnamed: D2.2 (A), TR1.4
unnamed: J1.10 (LEDG+), R2.1
unnamed: J1.11 (LEDY-), R1.1
unnamed: J2.10 (LEDG+), R6.1
unnamed: J2.12 (LEDY+), R5.1
unnamed: R9.1, TR1.1
unnamed: R10.1, TR1.3
unnamed: J1.4, U1.2 (SCLA)
unnamed: J1.3, U1.3 (SDAA)
unnamed: R10.2, U3.1 (VD1)
unnamed: R9.2, U3.3 (VD2)
VCC: C1.1, C3.1, J1.5, J1.6, J1.7, J1.8, J2.5, J2.6, J2.7, J2.8, R2.2, R3.2, R4.2, R6.2, TR1.2, U1.1 (VCCA), U1.5 (EN), U1.8 (VCCB), U2.1 (VCC1), U3.2 (VCC), U3.5 (EN)

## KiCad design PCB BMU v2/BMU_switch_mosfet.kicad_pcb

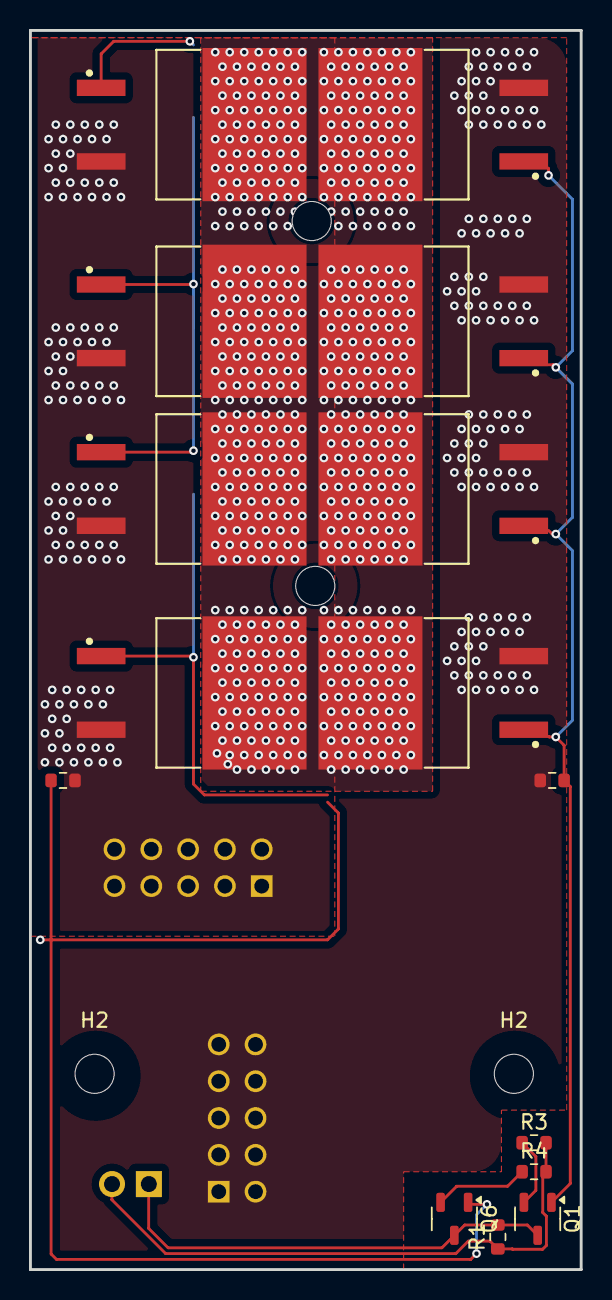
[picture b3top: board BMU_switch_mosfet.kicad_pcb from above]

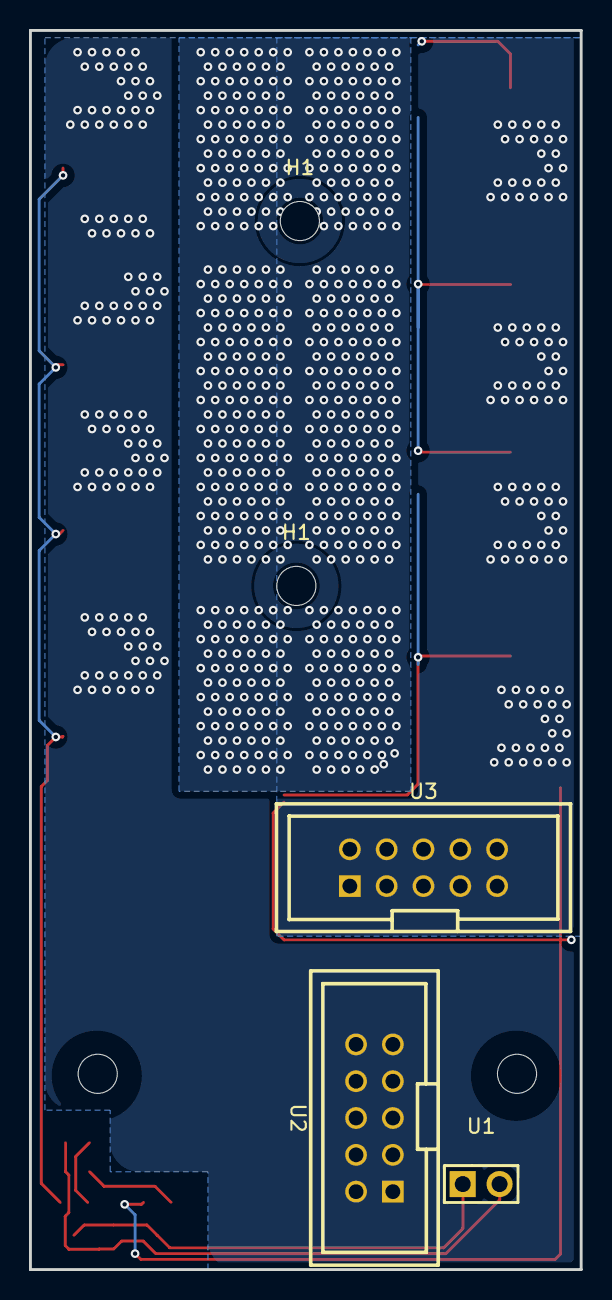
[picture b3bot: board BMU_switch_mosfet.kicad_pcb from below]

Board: 2 copper layers, 38.0 x 85.5 mm, 22 parts (5 on the bottom side), 9 nets.

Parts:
H1, H1#2, H2, H2#2: MountingHole; MountingHole_2.7mm_M2.5
Q1, Q6: BC337; SOT-23-3
Q2, Q3, Q4, Q5, Q7, Q8, Q9, Q10: IRF4905STRLPBF; D2PAK_L9.1-W10.0-P2.54-LS15.3-TL
R1, R2, R3, R4, R5: 10K; R_0603_1608Metric
U1: HX PZ2.54-1X2P ZZ; HDR-TH_2P-P2.54-V-M-3
U2, U3: ZX-IDC2.54-2-5PZZ; IDC-TH_10P-P2.54_ZX-IDC2.54-2-5PZZ

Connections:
/+BATT OUT: Q7.3 (S), Q8.3 (S), Q9.3 (S), Q10.3 (S), R5.2, U3.1, U3.2, U3.3, U3.4, U3.5, U3.6, U3.7, U3.8, U3.9, U3.10
/+BATT_IN: Q2.3 (S), Q3.3 (S), Q4.3 (S), Q5.3 (S), R2.2, U2.1, U2.2, U2.3, U2.4, U2.5, U2.6, U2.7, U2.8, U2.9, U2.10
/CMD_Switch_bat: R1.1, R3.2, R4.2, U1.2
/Drain: Q2.4 (D), Q3.4 (D), Q4.4 (D), Q5.4 (D), Q7.4 (D), Q8.4 (D), Q9.4 (D), Q10.4 (D)
GND: Q1.3 (E), Q6.3 (E), R1.2, U1.1
unnamed: Q1.2 (B), R3.1
unnamed: Q1.1 (C), Q2.1 (G), Q3.1 (G), Q4.1 (G), Q5.1 (G), R2.1
unnamed: Q6.2 (B), R4.1
unnamed: Q6.1 (C), Q7.1 (G), Q8.1 (G), Q9.1 (G), Q10.1 (G), R5.1

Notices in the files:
README.md:
License: GPLv3
